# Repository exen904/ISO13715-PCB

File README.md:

# ISO13715 Macropad

Name derives from DIN ISO 13715 ```Kanten mit unbestimmter Gestalt```. Depending on the layout you choose for the bottom row 13/15 keys, 7 where the regular Alpha cluster would be and ISO should be obvious. 

Huge shoutout to PCBway, who sponsored the run of the matte black PCB I used in the build guide. No strings attached here, if you want a matte black PCB, thats the way to go.

## PCB
You can find the Gerber files for ordering your own PCB in the `PCB\production` folder. For service I can absolutely recommend PCBway, who as mentioned above, sponsored my prototype run. Service was great and they deliver quality work, so I can really recommend them.

## BOM
- 15x SOD123 Diodes
- 3x SK-6812 MINI-E
- 2x 2U PCB mounted Stabilizers
- 1x MCU of your choice
- 8x 3x3mm magnets for the case
- 4-6x M2x3 heat inserts (4 should be more than fine)
- 4-6x M2x4 screws

For the MCU you have two options. Either XIAO RP2040, or Waveshare RP2040 Zero/0xCB Gemini. Both fit and work, however the pinout is mirrored on either option. I originally designed the PCB for the Xiao, with the MCU facing towards you (not like most split builds with face down MCUs). However, my Proto is built with a RP2040 zero, which has to be flipped on its face. I recommend using IC sockets for the MCU. 

## Case
The current case only supports the HHKB bottom row with 2x 1U keys, the version with the larger blockers is still on my todo. If you cant wait though, feel free to edit the STEP files to your needs. For the diffusor, I chose transparent PETG and for a more unified look, changed the last layer to white. The mounting system of the case itself is inspired from the awesome cases from Bubbleology and uses the same magnets.

For printing, I recommend 0.2mm layer height, anything around 10% infill. How tight the plate works for you also depends on the swichtes you choose, if its too loose you can play around with the XY Hole compensation in your slicer.

## Firmware
I started with a very basic KMK firmware based of POG to test everything, which is still included here in the Repo. However, now I also finished the QMK-VIAL port for the board. I only tested this on a 0xCB Gemini, not on a Xiao RP2040. As the Xiao exposes different pins, those need to be changed before compiling the firmware. I currently dont have one on hand to test, so Im not going to provide untested firmware files. Please adjust here for yourself.

If you are using a Helios/RP2040 Zero, you can use the provided `iso13715_vial_gemini.uf2` in the `Firmware` folder. The VIAL firmware also has bootmagic enabled, so to get into bootloader mode, you just need to hold down the imaginary `ESC` key on the board.

### KLE layout options

## Build Guide
[You can find the build guide for the PCB here](https://github.com/exen904/ISO13715-PCB/blob/main/build_guide.md)

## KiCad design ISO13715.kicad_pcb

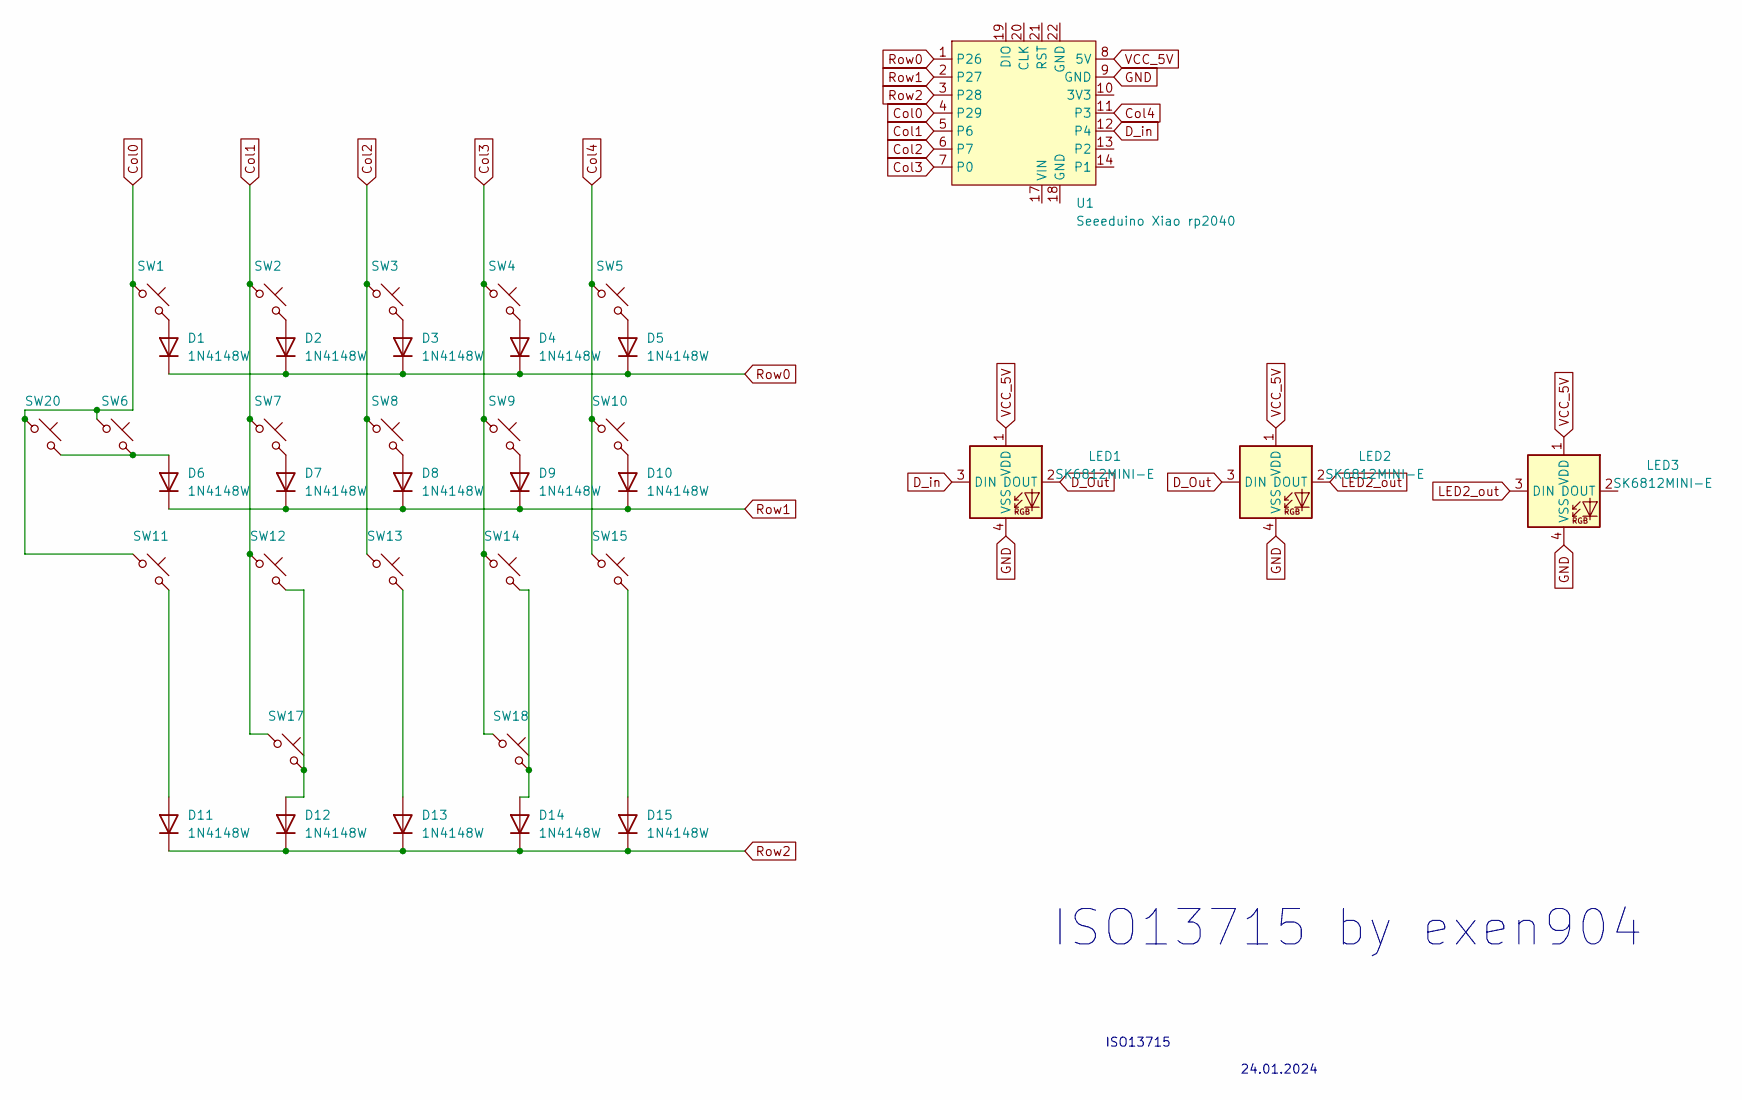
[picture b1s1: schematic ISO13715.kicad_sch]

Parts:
D1, D2, D3, D4, D5, D6, D7, D8, D9, D10, D11, D12, D13, D14, D15: 1N4148W; D_SOD-123
LED1, LED2, LED3: SK6812MINI-E; LED_6028R
SW1, SW2, SW3, SW4, SW5, SW7, SW8, SW9, SW10, SW11, SW12, SW13, SW14, SW15: SW_MX_1u
SW6, SW20: SW_MX_1.75u
SW17, SW18: SW_MX_1.25u
U1: Seeeduino Xiao rp2040; Xiao_rp2040_AH_Pogo

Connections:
Col0: SW1.1, SW6.1, SW11.1, SW20.1, U1.4 (P29)
Col1: SW2.1, SW7.1, SW12.1, SW17.1, U1.5 (P6)
Col2: SW3.1, SW8.1, SW13.1, U1.6 (P7)
Col3: SW4.1, SW9.1, SW14.1, SW18.1, U1.7 (P0)
Col4: SW5.1, SW10.1, SW15.1, U1.11 (P3)
D_Out: LED1.2 (DOUT), LED2.3 (DIN)
D_in: LED1.3 (DIN), U1.12 (P4)
GND: LED1.4 (VSS), LED2.4 (VSS), LED3.4 (VSS), U1.9 (GND)
LED2_out: LED2.2 (DOUT), LED3.3 (DIN)
unnamed: D1.2 (A), SW1.2
unnamed: D2.2 (A), SW2.2
unnamed: D3.2 (A), SW3.2
unnamed: D4.2 (A), SW4.2
unnamed: D5.2 (A), SW5.2
unnamed: D6.2 (A), SW6.2, SW20.2
unnamed: D7.2 (A), SW7.2
unnamed: D8.2 (A), SW8.2
unnamed: D9.2 (A), SW9.2
unnamed: D10.2 (A), SW10.2
unnamed: D11.2 (A), SW11.2
unnamed: D12.2 (A), SW12.2, SW17.2
unnamed: D13.2 (A), SW13.2
unnamed: D14.2 (A), SW14.2, SW18.2
unnamed: D15.2 (A), SW15.2
Row0: D1.1 (K), D2.1 (K), D3.1 (K), D4.1 (K), D5.1 (K), U1.1 (P26)
Row1: D6.1 (K), D7.1 (K), D8.1 (K), D9.1 (K), D10.1 (K), U1.2 (P27)
Row2: D11.1 (K), D12.1 (K), D13.1 (K), D14.1 (K), D15.1 (K), U1.3 (P28)
VCC_5V: LED1.1 (VDD), LED2.1 (VDD), LED3.1 (VDD), U1.8 (5V)

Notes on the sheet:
ISO13715 by exen904
24.01.2024
ISO13715

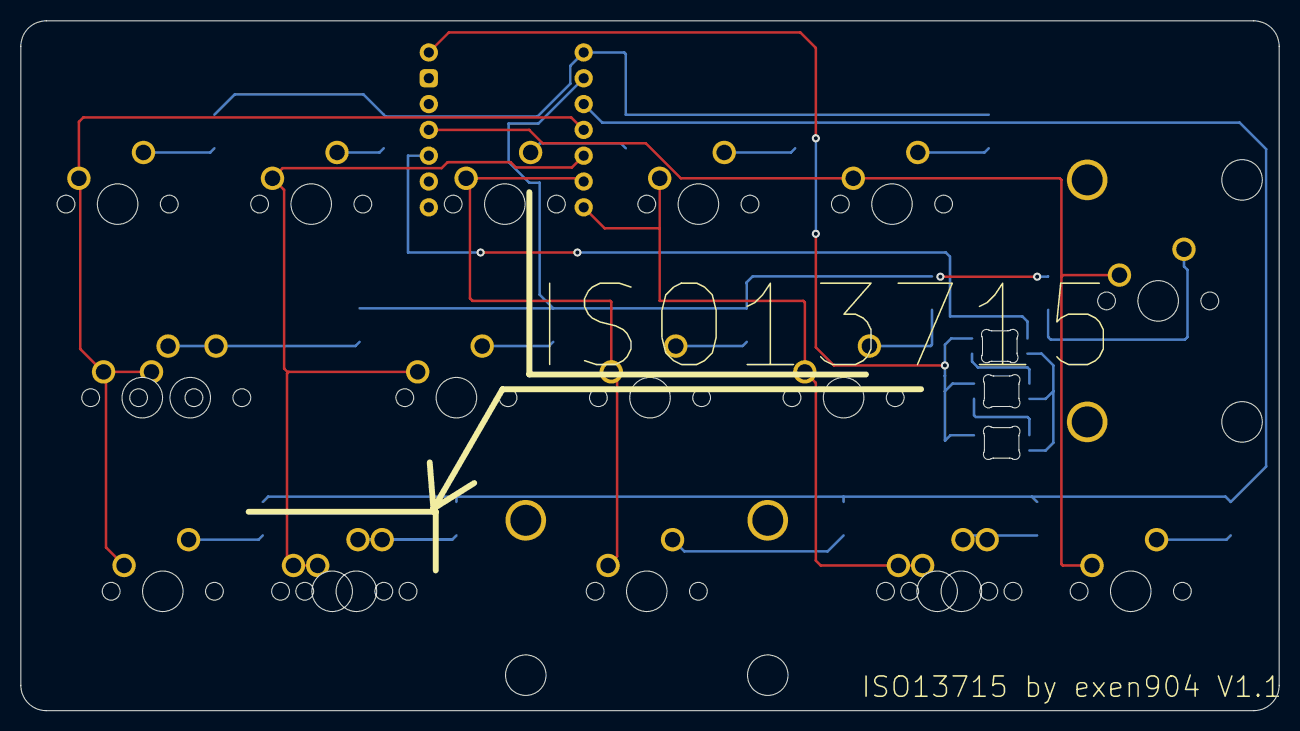
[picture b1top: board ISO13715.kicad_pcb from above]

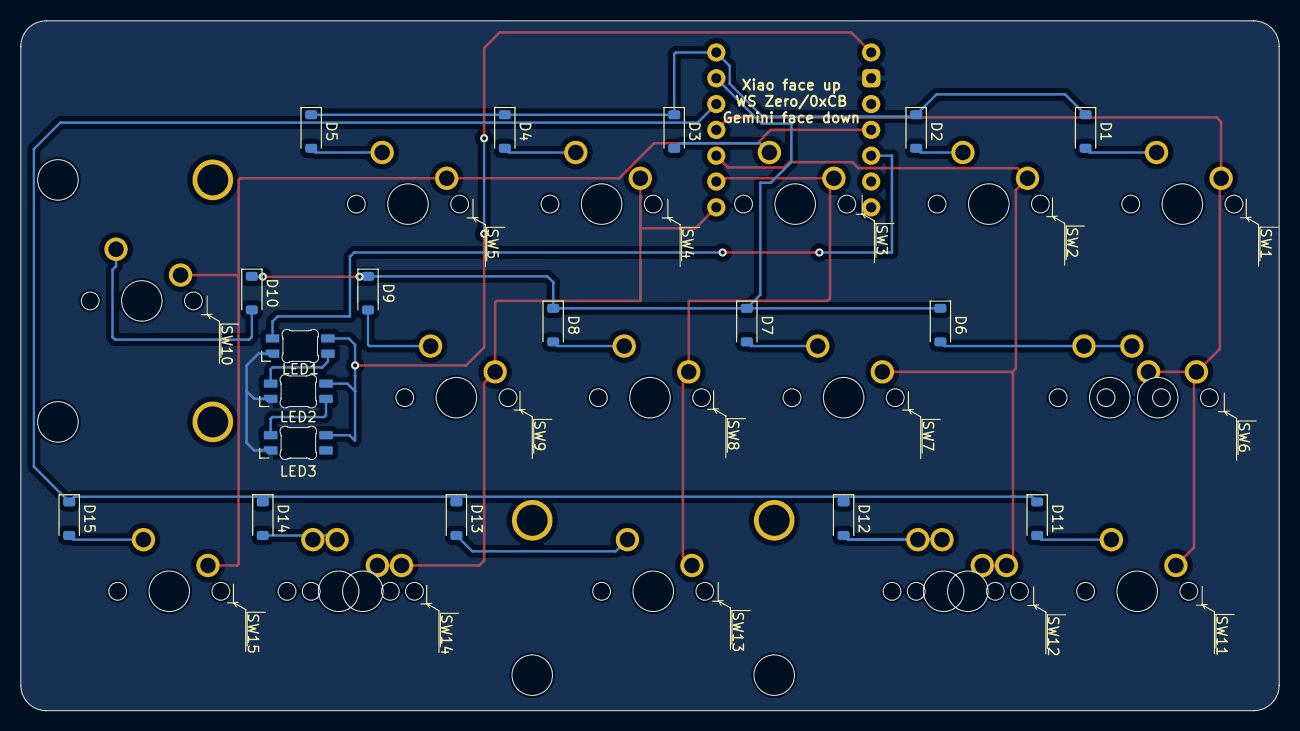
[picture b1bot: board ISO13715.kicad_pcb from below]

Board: 2 copper layers, 123.8 x 67.9 mm, 37 parts (19 on the bottom side), 28 nets.

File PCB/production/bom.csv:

Designator,Footprint,Quantity,Value,LCSC Part #
"D1, D10, D11, D12, D13, D14, D15, D2, D3, D4, D5, D6, D7, D8, D9",D_SOD-123,15,1N4148W,
"LED1, LED2, LED3",LED_6028R,3,SK6812MINI-E,
"SW1, SW6",SW_MX_1u,2,~,
"SW10, SW11, SW12, SW13, SW14, SW15, SW2, SW3, SW4, SW5, SW7, SW8, SW9",SW_MX_1u_3D,13,~,
"SW17, SW18",SW_MX_1.25u,2,~,
SW20,SW_MX_1.75u_STP_1.25,1,~,

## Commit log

2024-02-21 update to pcb
2024-02-21 added readme
2024-02-21 changed GND to plane
2024-02-21 update ignore
2024-02-21 ignore
2024-11-07 updated PCB and readme
2024-11-07 added case
2024-11-07 added POG KMK files
2024-12-19 created build guide
2024-12-19 build guide link to readme
2025-02-17 updated case files to new magnet version
2025-02-17 updated pictures and readme
2025-02-17 readme
2025-02-17 production
2025-02-18 added VIAL and cleanup
